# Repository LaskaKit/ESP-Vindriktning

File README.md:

# LASKAKIT ESP-VINDRIKTNING

Ikea Vindriktning is very good and really cheap product which is able to show the quality of air in the room by three LEDs. The original Vindriktning just measure the dust. 
It is not so much for customer. 

We decided to create our own replaced board what will be compatible with the original board but add with Wi-Fi and Bluetooth connectivity, optionaly more sensors, and addressable LEDs. Thanks to this, you get powerful product what may measure the quality of air in the details. 

## Programming
The LASKAKIT ESP-VINDRIKTNING as well as Ikea Vindriktning includes USB-C connector. The orginal board is using the USB-C just for power supply, the ESP-VINDRIKTNING is using USB-C for power and also for programming, because the board includes built-in USB-UART IC as programmer. 

## Connectors
The LASKAKIT ESP-VINDRIKTNING contains six connectors. Two of them are used for original dust sensor - sensor and fan. The third connector is called μŠup and it is compatible with STEMMA QT and Qwiic JST-SH. Thanks to this connector, you can add [temperature/humidity sensor SHT40](https://www.laskakit.cz/laskakit-sht40-senzor-teploty-a-vlhkosti-vzduchu/) or [SCD41 (sensor of CO2/temperature/humidity)](https://www.laskakit.cz/laskakit-scd41-senzor-co2--teploty-a-vlhkosti-vzduchu/) and improve the measurement of air. 
Fourth connector is just 4pin header and you can solder what you want. The 4pin connector includes I2C and power supply with 3.3V. 
The reset of the connectors contains power supply (3.3V) and GPIO which you can use for your purpose. Also the hardware SPI may be used from this connector. 

## LEDs
The number of LEDs is the same with original board. The LEDs are RGB and addressable, it means you can define the color on separately each LED. At the end, you can indicate dust on the first LED, CO2 on the second LED and temperature on third LED. 

## Example codes 
For the fastest development, we prepared a few examples where we show how to easily use LASKAKIT ESP-VINDRIKTNING alone or with SCD41
Use "nodemcu-32s" board in ESPHome and "ESP32 Dev Module" in Arduino IDE.

## Link
The product is available on our store https://www.laskakit.cz/laskakit-esp-vindriktning-esp-32-i2c/
Optional parts: 

SCD41 (CO2/temperature/humidity) https://www.laskakit.cz/laskakit-scd41-senzor-co2--teploty-a-vlhkosti-vzduchu/

SHT40 (temperature/humidity) https://www.laskakit.cz/laskakit-sht40-senzor-teploty-a-vlhkosti-vzduchu/

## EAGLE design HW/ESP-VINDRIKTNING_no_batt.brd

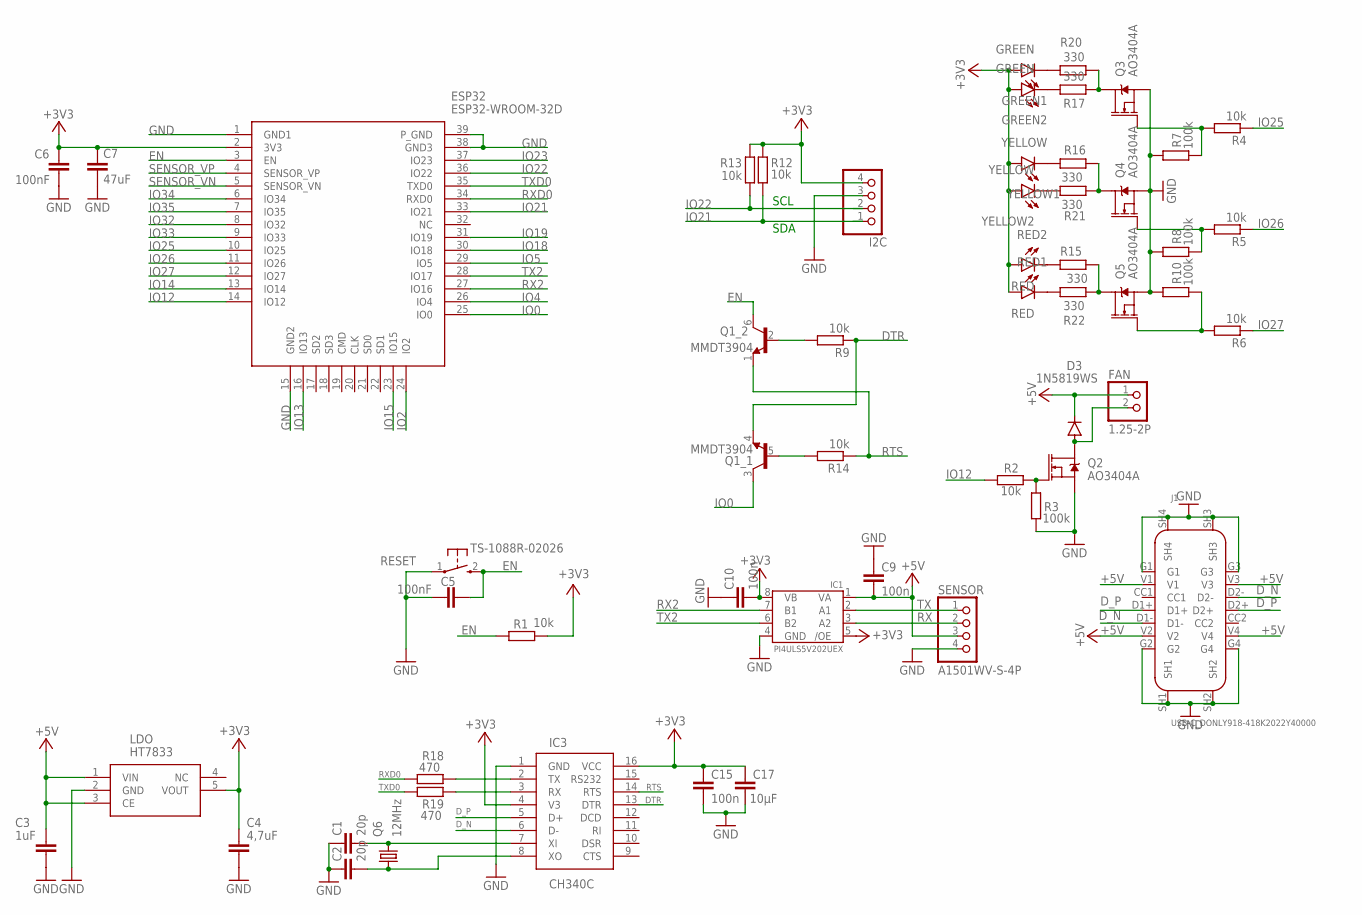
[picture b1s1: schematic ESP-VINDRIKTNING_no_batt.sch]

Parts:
C1, C2: 20p; C0402
C3: 1uF; C0603
C4: 4,7uF; C0603; LCSC_PART C19666
C5: 100nF; C0402
C6: 100nF; C0603
C7: 47uF; C0603; LCSC_PART C122913
C9, C10, C15: 100n; C0603
C17: 10μF; C0603
D3: 1N5819WS; SOD323-R
ESP32: ESP32-WROOM-32D; ESP32WROOM32D; LCSC_PART C82899
FAN: 1.25-2P
GREEN1, GREEN2: GREEN; CHIP-LED0603
I2C: PINHD-1X4; 1X04; LCSC_PART C2321
IC1: PI4ULS5V202UEX; MSOP8
IC3: CH340C; SOIC16
J1: USB-C_DONLY918-418K2022Y40000; USB-C-TH
LDO: HT7833; SOT23-5
Q1: MMDT3904; SC70-6; LCSC_PART C268586
Q2, Q3, Q4, Q5: AO3404A; SOT23-3
Q6: 12MHz; 3.2X2.5_KX-7; LCSC_PART C97242
R1, R2, R4, R5, R6, R9, R14: 10k; R0402
R3, R7, R8, R10: 100k; R0402
R12, R13: 10k; R0603
R15, R16, R17, R20, R21, R22: 330; R0603
R18, R19: 470; R0402
RED1, RED2: RED; CHIP-LED0603
RESET: TS-1088R-02026; TS1088R02026
SENSOR: A1501WV-S-4P
YELLOW1, YELLOW2: YELLOW; CHIP-LED0603

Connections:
+3V3: C4.1, C6.1, C7.1, C10.2, C15.1, C17.1, ESP32.2 (3V3), GREEN1.A, GREEN2.A, I2C.4, IC1.5 (/OE), IC1.8 (VB), IC3.4 (V3), IC3.16 (VCC), LDO.5 (VOUT), R1.1, R12.2, R13.2, RED1.A, RED2.A, YELLOW1.A, YELLOW2.A
+5V: C3.1, C9.2, D3.C, FAN.1, IC1.1 (VA), J1.V1, J1.V2, J1.V3, J1.V4, LDO.1 (VIN), LDO.3 (CE), SENSOR.3
DTR: IC3.13 (DTR), Q1.4 (E), R9.1
D_N: IC3.6 (D-), J1.D1-, J1.D2-
D_P: IC3.5 (D+), J1.D1+, J1.D2+
EN: C5.2, ESP32.3 (EN), Q1.6 (C), R1.2, RESET.2 (3)
G: Q3.3 (D), R17.2, R20.2
GND: C1.1, C2.1, C3.2, C4.2, C5.1, C6.2, C7.2, C9.1, C10.1, C15.2, C17.2, ESP32.1 (GND1), ESP32.15 (GND2), ESP32.38 (GND3), ESP32.39 (P_GND), I2C.3, IC1.4 (GND), IC3.1 (GND), J1.G1, J1.G2, J1.G3, J1.G4, J1.SH1, J1.SH2, J1.SH3, J1.SH4, LDO.2 (GND), Q2.2 (S), Q3.2 (S), Q4.2 (S), Q5.2 (S), R3.2, R7.1, R8.1, R10.1, RESET.1, SENSOR.4
IO0: ESP32.25 (IO0), Q1.3 (C)
IO2: ESP32.24 (IO2)
IO4: ESP32.26 (IO4)
IO5: ESP32.29 (IO5)
IO12: ESP32.14 (IO12), R2.2
IO13: ESP32.16 (IO13)
IO14: ESP32.13 (IO14)
IO15: ESP32.23 (IO15)
IO18: ESP32.30 (IO18)
IO19: ESP32.31 (IO19)
IO21: ESP32.33 (IO21), I2C.1, R12.1
IO22: ESP32.36 (IO22), I2C.2, R13.1
IO23: ESP32.37 (IO23)
IO25: ESP32.10 (IO25), R4.1
IO26: ESP32.11 (IO26), R5.1
IO27: ESP32.12 (IO27), R6.1
IO32: ESP32.8 (IO32)
IO33: ESP32.9 (IO33)
IO34: ESP32.6 (IO34)
IO35: ESP32.7 (IO35)
unnamed: GREEN1.C, R20.1
unnamed: D3.A, FAN.2, Q2.3 (D)
unnamed: Q2.1 (G), R2.1, R3.1
unnamed: C1.2, IC3.7 (XI), Q6.3 (2)
unnamed: Q1.5 (B), R14.2
unnamed: Q5.1 (G), R6.2, R10.2
unnamed: Q4.1 (G), R5.2, R8.2
unnamed: R21.2, YELLOW2.C
unnamed: Q1.2 (B), R9.2
unnamed: R15.1, RED2.C
unnamed: R16.2, YELLOW1.C
unnamed: R22.1, RED1.C
unnamed: GREEN2.C, R17.1
unnamed: Q3.1 (G), R4.2, R7.2
unnamed: C2.2, IC3.8 (XO), Q6.1
unnamed: IC3.2 (TX), R18.2
unnamed: IC3.3 (RX), R19.2
R: Q5.3 (D), R15.2, R22.2
RTS: IC3.14 (RTS), Q1.1 (E), R14.1
RX: IC1.3 (A2), SENSOR.2
RX2: ESP32.27 (IO16), IC1.7 (B1)
RXD0: ESP32.34 (RXD0), R18.1
SENSOR_VN: ESP32.5 (SENSOR_VN)
SENSOR_VP: ESP32.4 (SENSOR_VP)
TX: IC1.2 (A1), SENSOR.1
TX2: ESP32.28 (IO17), IC1.6 (B2)
TXD0: ESP32.35 (TXD0), R19.1
Y: Q4.3 (D), R16.1, R21.1

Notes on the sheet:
SDA
SCL

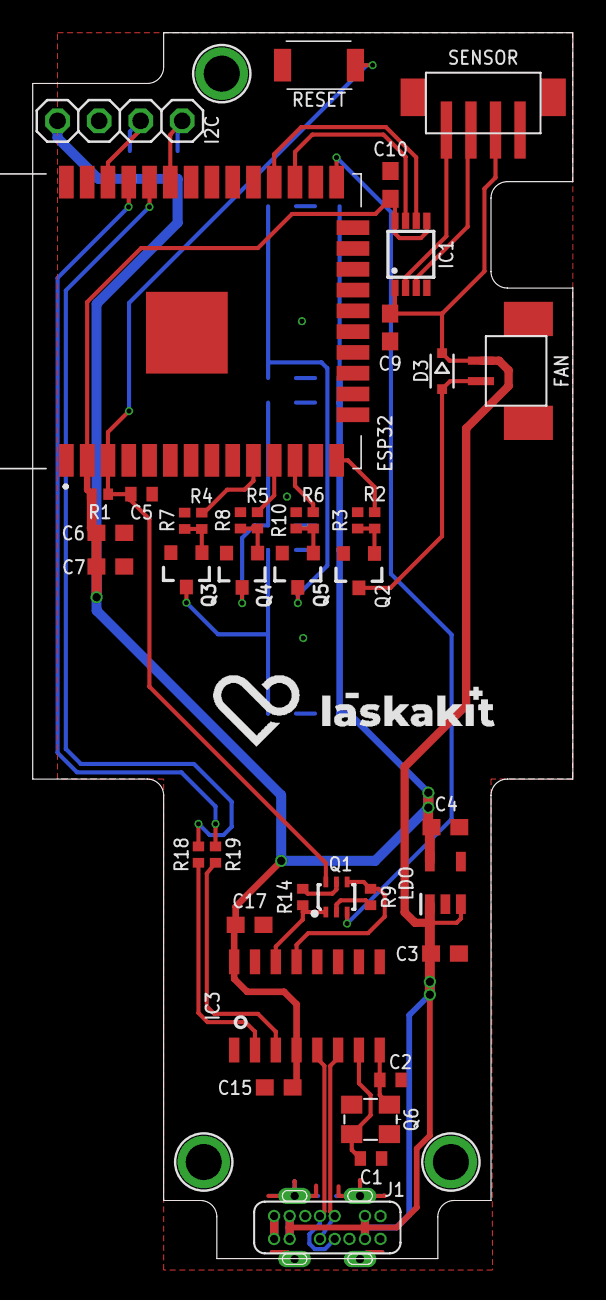
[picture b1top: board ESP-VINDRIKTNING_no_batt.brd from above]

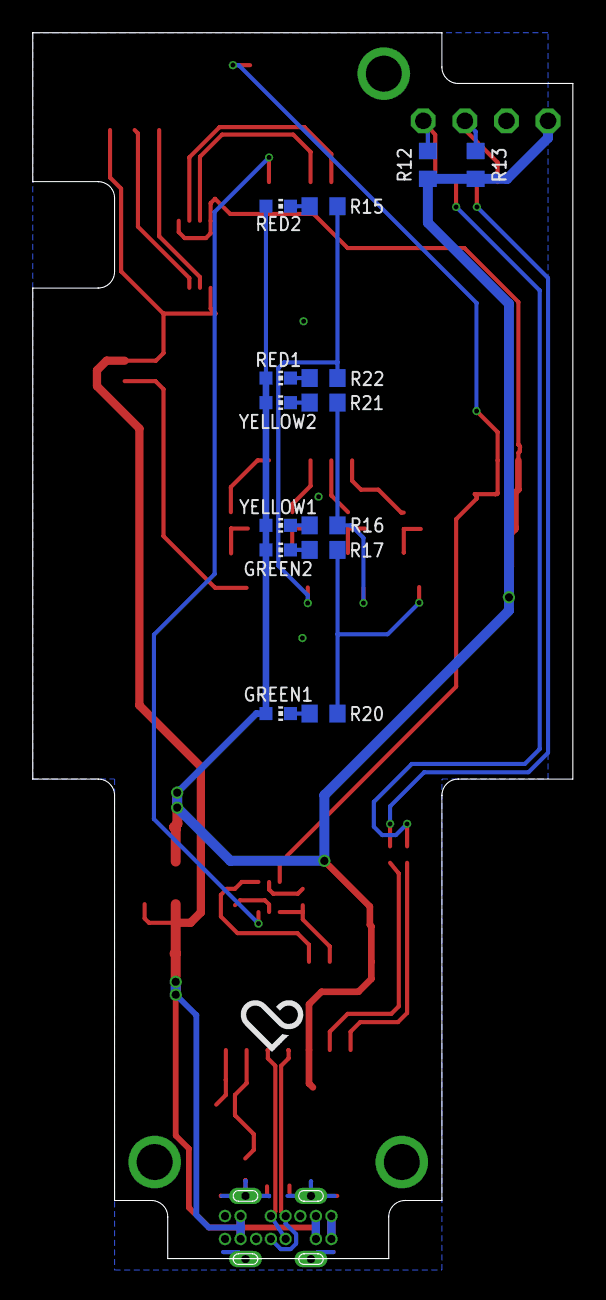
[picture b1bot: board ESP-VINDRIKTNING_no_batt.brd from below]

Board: 2 copper layers, 33.0 x 75.3 mm, 56 parts (15 on the bottom side), 41 nets.

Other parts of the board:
U$1: LASKKIT_20MM_SILKSCREEN
U$2: LASKAKIT_HEART_4MM

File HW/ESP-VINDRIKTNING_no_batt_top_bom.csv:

Comment,Designator,Footprint,LCSC Part #
1.25-2P,D1 D3 FAN,1.25-2P,C393945
1uF,C3,C0603,
2k7,R5,R0402,
4 7uF,C4,C0603,C50936
4k7,R3,R0402,
10k,R1 R2 R4 R9 R12 R13 R14,R0402,
10uF,C2,C0603,
10μF,C17,C0603,
100n,C9 C10 C15,C0603,
100nF,C1,C0603,
100nF,C5,C0402,
470,R8,R0402,
470,R18 R19,R0603,
A1501WV-S-4P,SENSOR,A1501WV-S-4P,C225162
CH340C,IC3,SOIC16,
DMG2305UX,Q6,SUPER-SOT3,C144153
ESP-12S,U1,ESP12-SMD,
HT7833,LDO,SOT23-5,
JUMPER-SMT_2_NO_NO-SILK,SLEEP,SMT-JUMPER_2_NO_NO-SILK,
MMDT3904,Q1,SC70-6,C268586
PI4ULS5V202UEX,IC1,MSOP8,C481697
TS-1088R-02026,RESET,TS1088R02026,

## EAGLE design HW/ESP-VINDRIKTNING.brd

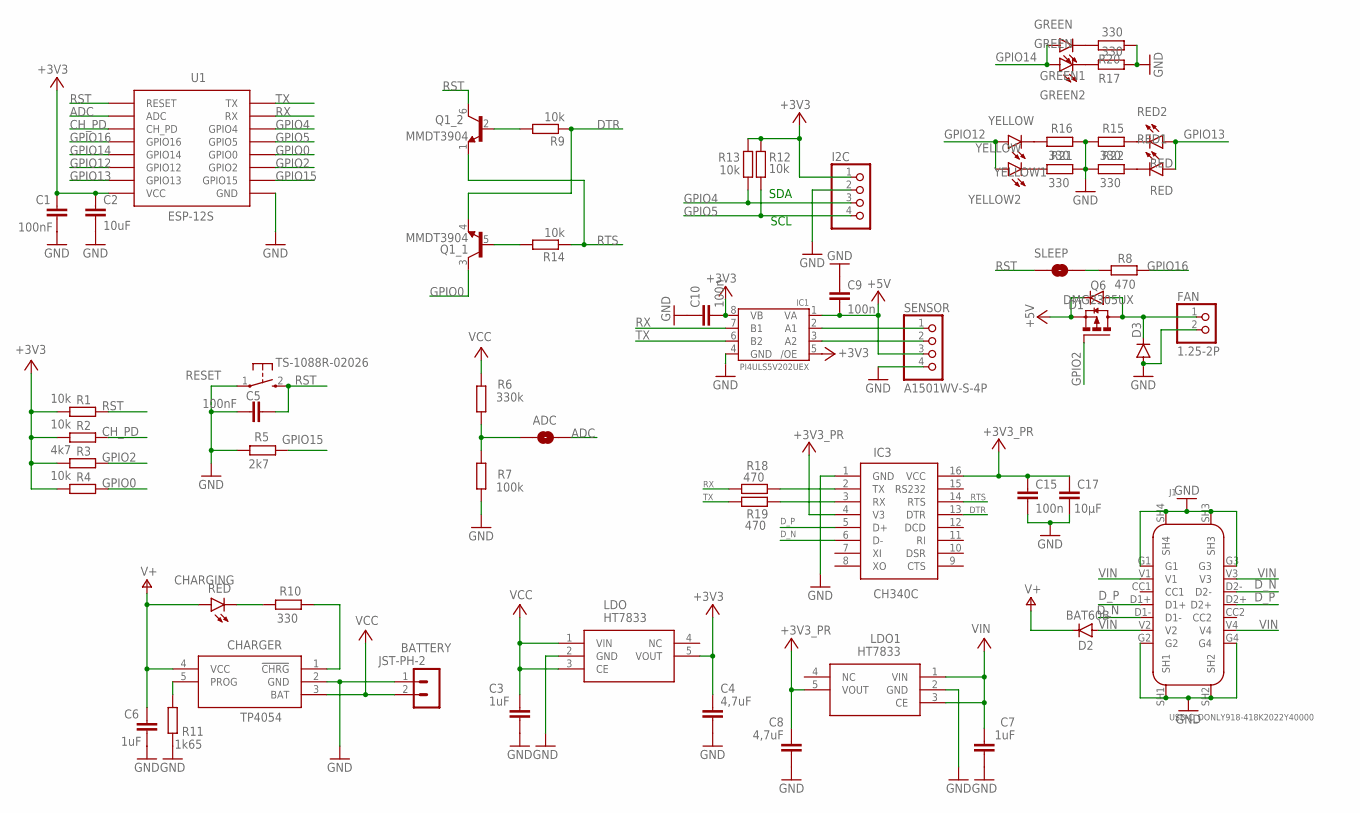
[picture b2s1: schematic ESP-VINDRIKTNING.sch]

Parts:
ADC: JUMPER-SMT_2_NO_NO-SILK; SMT-JUMPER_2_NO_NO-SILK
BATTERY: JST-PH-2; B2B-PH-K
C1: 100nF; C0603
C2: 10uF; C0603
C3, C6, C7: 1uF; C0603
C4, C8: 4,7uF; C0603; LCSC_PART C50936
C5: 100nF; C0402
C9, C10, C15: 100n; C0603
C17: 10μF; C0603
CHARGER: TP4054; SOT-23-5
CHARGING: RED; CHIPLED_0603
D1, D3: DIODE-SOD323-R; SOD323-R
D2: BAT60B; SOD323-R
FAN: 1.25-2P
GREEN1, GREEN2: GREEN; CHIP-LED0603
I2C: PINHD-1X4; 1X04
IC1: PI4ULS5V202UEX; MSOP8
IC3: CH340C; SOIC16
J1: USB-C_DONLY918-418K2022Y40000; USB-C-TH
LDO, LDO1: HT7833; SOT23-5
Q1: MMDT3904; SC70-6; LCSC_PART C268586
Q6: DMG2305UX; SUPER-SOT3; LCSC_PART C144153
R1, R2, R4, R9, R12, R13, R14: 10k; R0402
R3: 4k7; R0402
R5: 2k7; R0402
R6: 330k; R0402
R7: 100k; R0402
R8: 470; R0402
R10: 330; R0603
R11: 1k65; R0603
R15, R16, R17, R20, R21, R22: 330; R0402
R18, R19: 470; R0603
RED1, RED2: RED; CHIP-LED0603
RESET: TS-1088R-02026; TS1088R02026
SENSOR: A1501WV-S-4P
SLEEP: JUMPER-SMT_2_NO_NO-SILK; SMT-JUMPER_2_NO_NO-SILK
U1: ESP-12S; ESP12-SMD
YELLOW1, YELLOW2: YELLOW; CHIP-LED0603

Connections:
+3V3: C1.1, C2.1, C4.1, C10.2, I2C.1, IC1.5 (/OE), IC1.8 (VB), LDO.5 (VOUT), R1.1, R2.1, R3.1, R4.1, R12.2, R13.2, U1.VCC
+3V3_PR: C8.1, C15.1, C17.1, IC3.4 (V3), IC3.16 (VCC), LDO1.5 (VOUT)
+5V: C9.2, D1.C, IC1.1 (VA), Q6.2 (S), SENSOR.3
ADC: ADC.2, U1.ADC
CH_PD: R2.2, U1.CH_PD
DTR: IC3.13 (DTR), Q1.4 (E), R9.1
D_N: IC3.6 (D-), J1.D1-, J1.D2-
D_P: IC3.5 (D+), J1.D1+, J1.D2+
GND: BATTERY.1 (2), C1.2, C2.2, C3.2, C4.2, C5.1, C6.2, C7.2, C8.2, C9.1, C10.1, C15.2, C17.2, CHARGER.2 (GND), D3.A, FAN.2, I2C.2, IC1.4 (GND), IC3.1 (GND), J1.G1, J1.G2, J1.G3, J1.G4, J1.SH1, J1.SH2, J1.SH3, J1.SH4, LDO.2 (GND), LDO1.2 (GND), R5.2, R7.1, R11.1, R15.2, R16.1, R17.2, R20.2, R21.1, R22.2, RESET.1, SENSOR.4, U1.GND
GPIO0: Q1.3 (C), R4.2, U1.GPIO0
GPIO2: Q6.1 (G), R3.2, U1.GPIO2
GPIO4: I2C.3, R13.1, U1.GPIO4
GPIO5: I2C.4, R12.1, U1.GPIO5
GPIO12: U1.GPIO12, YELLOW1.A, YELLOW2.A
GPIO13: RED1.A, RED2.A, U1.GPIO13
GPIO14: GREEN1.A, GREEN2.A, U1.GPIO14
GPIO15: R5.1, U1.GPIO15
GPIO16: R8.2, U1.GPIO16
unnamed: GREEN1.C, R20.1
unnamed: CHARGER.5 (PROG), R11.2
unnamed: ADC.1, R6.1, R7.2
unnamed: CHARGER.1 (!CHRG), R10.1
unnamed: CHARGING.C, R10.2
unnamed: R8.1, SLEEP.2
unnamed: Q1.5 (B), R14.2
unnamed: R21.2, YELLOW2.C
unnamed: Q1.2 (B), R9.2
unnamed: R15.1, RED2.C
unnamed: R16.2, YELLOW1.C
unnamed: R22.1, RED1.C
unnamed: GREEN2.C, R17.1
unnamed: D1.A, D3.C, FAN.1, Q6.3 (D)
unnamed: IC3.2 (TX), R18.2
unnamed: IC3.3 (RX), R19.2
RST: C5.2, Q1.6 (C), R1.2, RESET.2 (3), SLEEP.1, U1.RESET
RTS: IC3.14 (RTS), Q1.1 (E), R14.1
RX: IC1.7 (B1), R18.1, U1.RXD0 (RX)
RX_: IC1.2 (A1), SENSOR.1
TX: IC1.6 (B2), R19.1, U1.TXD0 (TX)
TX_: IC1.3 (A2), SENSOR.2
V+: C6.1, CHARGER.4 (VCC), CHARGING.A, D2.C
VCC: BATTERY.2 (1), C3.1, CHARGER.3 (BAT), LDO.1 (VIN), LDO.3 (CE), R6.2
VIN: C7.1, D2.A, J1.V1, J1.V2, J1.V3, J1.V4, LDO1.1 (VIN), LDO1.3 (CE)

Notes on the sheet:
SDA
SCL

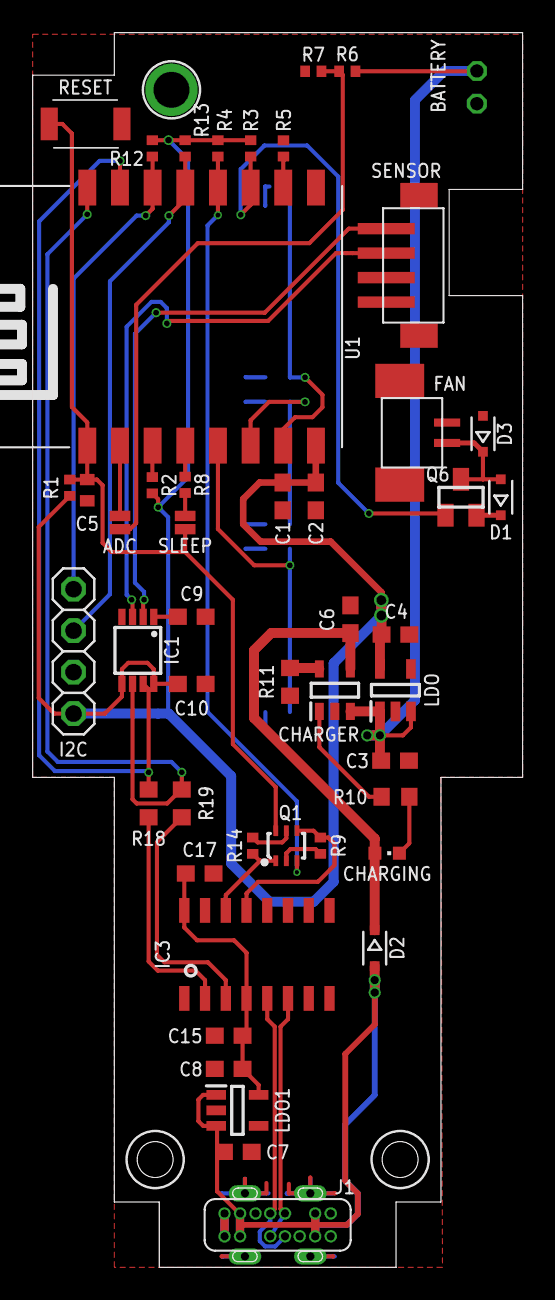
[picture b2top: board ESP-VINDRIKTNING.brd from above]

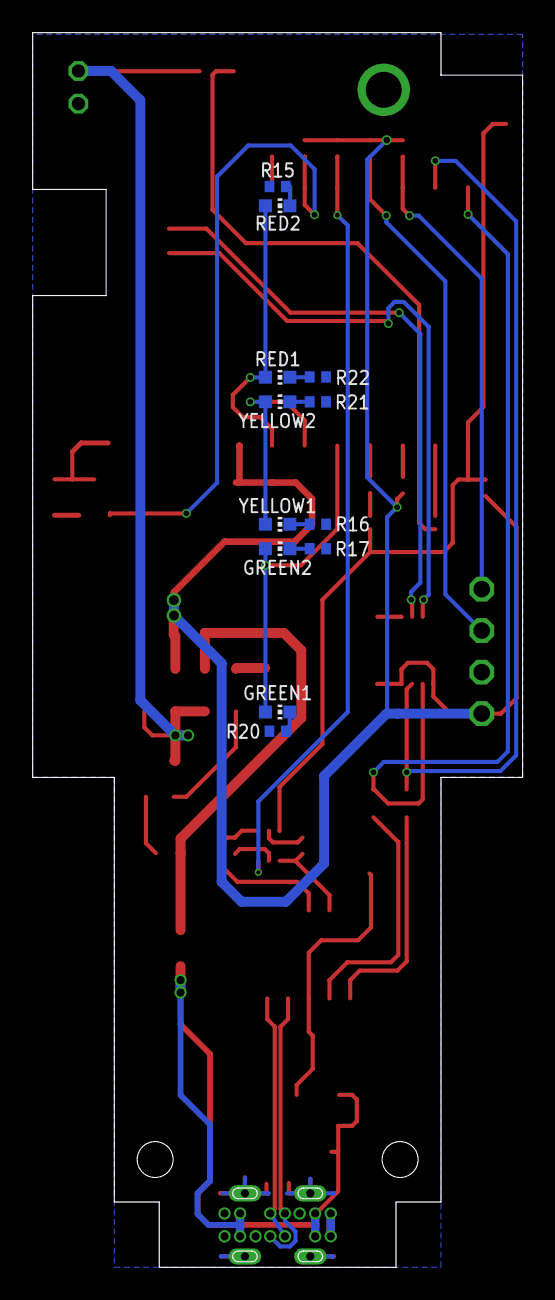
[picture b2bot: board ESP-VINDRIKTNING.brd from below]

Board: 2 copper layers, 30.0 x 75.6 mm, 60 parts (12 on the bottom side), 43 nets.

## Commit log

2021-10-14 ignore
2021-11-19 first working
2021-11-22 schematic
2021-12-08 connectors pos
2021-12-23 updaterd
2022-01-06 ws2812 added
2022-01-06 pics
2022-01-12 new data
2022-02-04 new LEDs
2022-02-04 license and readme
2022-02-04 old version with one color led
2022-02-04 clearing
2022-02-08 neopixel
2022-02-10 pm1006
2022-03-28 update data
2022-03-28 new connectors
2022-05-16 Rename ESP32-LPkit_Vindriktning_UART_TMEPcz.ino to ESP-Vindriktning_UART_TMEPcz.ino
2022-05-16 Rename SW/VINDRIKTNING/ESP32-LPkit_Vindriktning_UART_TMEPcz/README.md to SW/VINDRIKTNING/ESP-Vindriktning_UART_TMEPcz
2022-05-16 Rename SW/VINDRIKTNING/ESP32-LPkit_Vindriktning_UART_TMEPcz/ESP-Vindriktning_UART_TMEPcz.ino to SW/VINDRIKTNING/ESP-Vindriktning_UART_TMEPcz/ESP-Vindriktning_UART_TMEPcz.ino
2022-05-16 Rename SW/VINDRIKTNING/ESP32-LPkit_Vindriktning_UART_TMEPcz/pm1006.cpp to SW/VINDRIKTNING/ESP-Vindriktning_UART_TMEPcz/pm1006.cpp
2022-05-16 Rename SW/VINDRIKTNING/ESP32-LPkit_Vindriktning_UART_TMEPcz/pm1006.h to SW/VINDRIKTNING/ESP-Vindriktning_UART_TMEPcz/pm1006.h
2022-05-18 new folder
2022-05-26 new photo
2022-05-30 Update ESP-Vindriktning_UART_TMEPcz.ino
    Added code for RGB LED
    1th is used for pm2.5, 2nd for temperature, 3rd for CO2
2022-06-06 sw update
2022-06-06 old version
2022-06-06 old v1
2022-06-08 version added
2022-11-14 Rename ESP-Vindriktning_UART_TMEPcz.ino to ESP-Vindriktning_UART_TMEPcz_SCD41.ino
2022-11-14 Create ESP-Vindriktning_UART_TMEPcz_SHT40.ino
    LaskaKit sensor SHT40 instead of SCD41.
2022-12-14 new-version-test
2022-12-21 terst data
2023-02-10 new data and folders
2023-02-12 Fix spelling of μŠup in the README
2023-02-18 test data update
2023-03-08 photo update
2023-11-13 Update ESPHome.yaml
    The usage of the Uart2 is prohibited since the ESPHome 2023.4.0
2023-12-26 Create Vindriktning-all_in_one.ino
    Created all in one code that combines all other examples.
2023-12-27 Update Vindriktning-all_in_one.ino
    Fix timer. ESP is now just waiting (delay) and it is not sleeping. It has higher consumption but it is working.
2023-12-30 Fix #14 and #15 in basic example.
2023-12-30 Added new example that uses async approach instead of delay() everywhere.
2024-01-22 board info added
2024-03-27 uart2 is reserved
    ID 'uart2' is reserved internally and cannot be used
2024-08-14 new ver

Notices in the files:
parts and their libraries:
SparkFun-Aesthetics: Licensing: Creative Commons ShareAlike 4.0 International - https://creativecommons.org/licenses/by-sa/4.0
crystal-geyer_V1_0: Copyright: Geyer-Electronic
